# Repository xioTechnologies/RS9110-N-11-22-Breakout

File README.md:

RS9110-N-11-22-Breakout
=======================

Breakboard for the Redpine Signals [RS9110-N-11-22](http://www.redpinesignals.com/Modules/Internet_of_Things/Connection_Family/RS-9110-N-11-22.php) Wi-Fi module.  Includes pull-down resistors as per [datasheet](http://www.redpinesignals.com/pdfs/datasheets/RS9110-N-11-22_DataSheet.pdf) (pages 13-16).

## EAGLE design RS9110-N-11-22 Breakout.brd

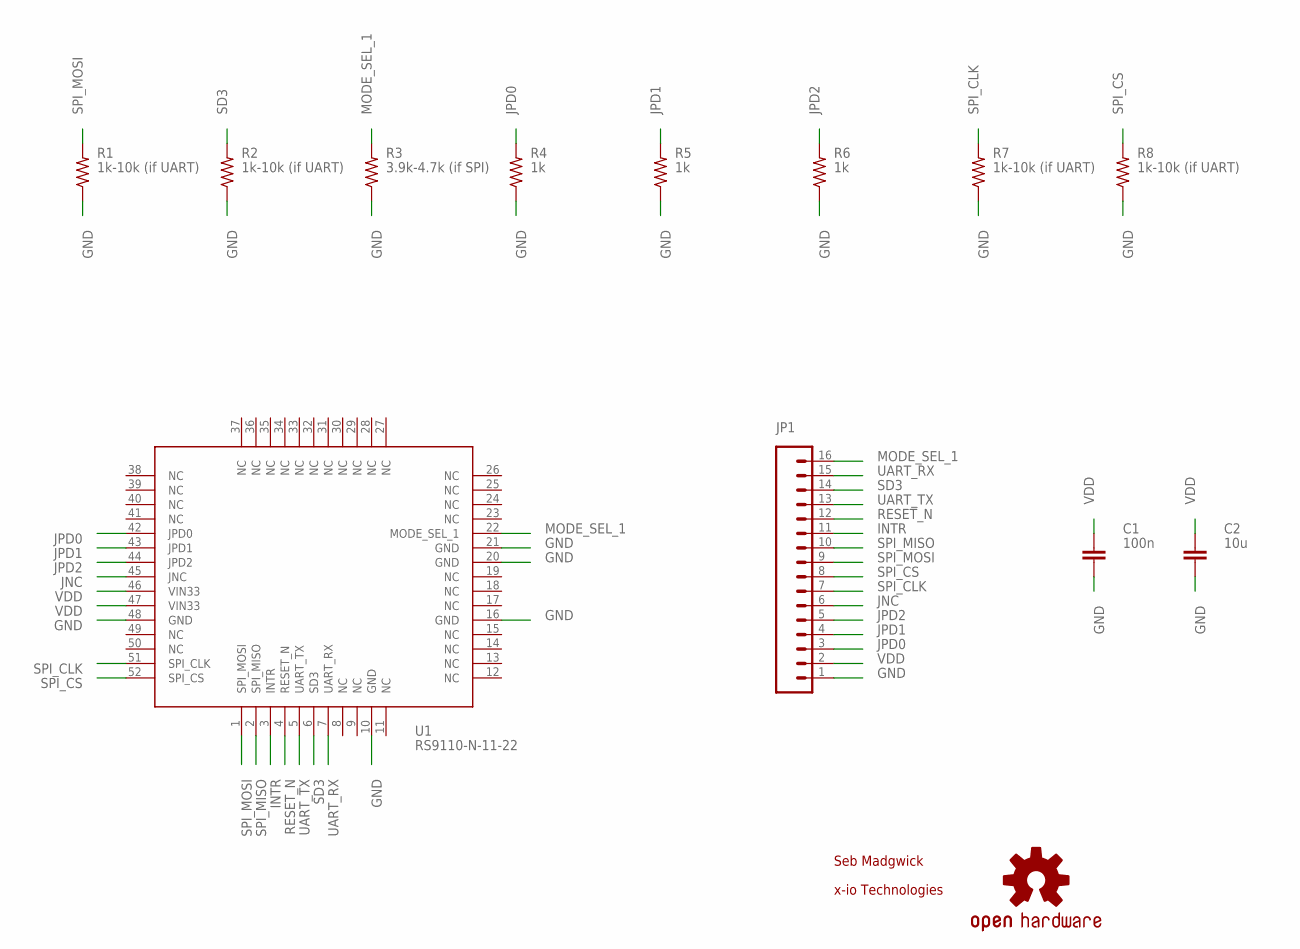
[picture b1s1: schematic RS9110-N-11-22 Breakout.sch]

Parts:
C1: 100n; 0603-CAP
C2: 10u; 0603-CAP
JP1: M16PTH; 1X16
LOGO1: OSHW-LOGOS; OSHW-LOGO-S
R1, R2, R7, R8: 1k-10k (if UART); 0603-RES
R3: 3.9k-4.7k (if SPI); 0603-RES
R4, R5, R6: 1k; 0603-RES
U1: RS9110-N-11-22

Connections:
GND: C1.2, C2.2, JP1.1, R1.1, R2.1, R3.1, R4.1, R5.1, R6.1, R7.1, R8.1, U1.10 (GND), U1.16 (GND), U1.20 (GND), U1.21 (GND), U1.48 (GND)
INTR: JP1.11, U1.3 (INTR)
JNC: JP1.6, U1.45 (JNC)
JPD0: JP1.3, R4.2, U1.42 (JPD0)
JPD1: JP1.4, R5.2, U1.43 (JPD1)
JPD2: JP1.5, R6.2, U1.44 (JPD2)
MODE_SEL_1: JP1.16, R3.2, U1.22 (MODE_SEL_1)
RESET_N: JP1.12, U1.4 (RESET_N)
SD3: JP1.14, R2.2, U1.6 (SD3)
SPI_CLK: JP1.7, R7.2, U1.51 (SPI_CLK)
SPI_CS: JP1.8, R8.2, U1.52 (SPI_CS)
SPI_MISO: JP1.10, U1.2 (SPI_MISO)
SPI_MOSI: JP1.9, R1.2, U1.1 (SPI_MOSI)
UART_RX: JP1.15, U1.7 (UART_RX)
UART_TX: JP1.13, U1.5 (UART_TX)
VDD: C1.1, C2.1, JP1.2, U1.46 (VIN33), U1.47 (VIN33)

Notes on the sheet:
Seb Madgwick
x-io Technologies

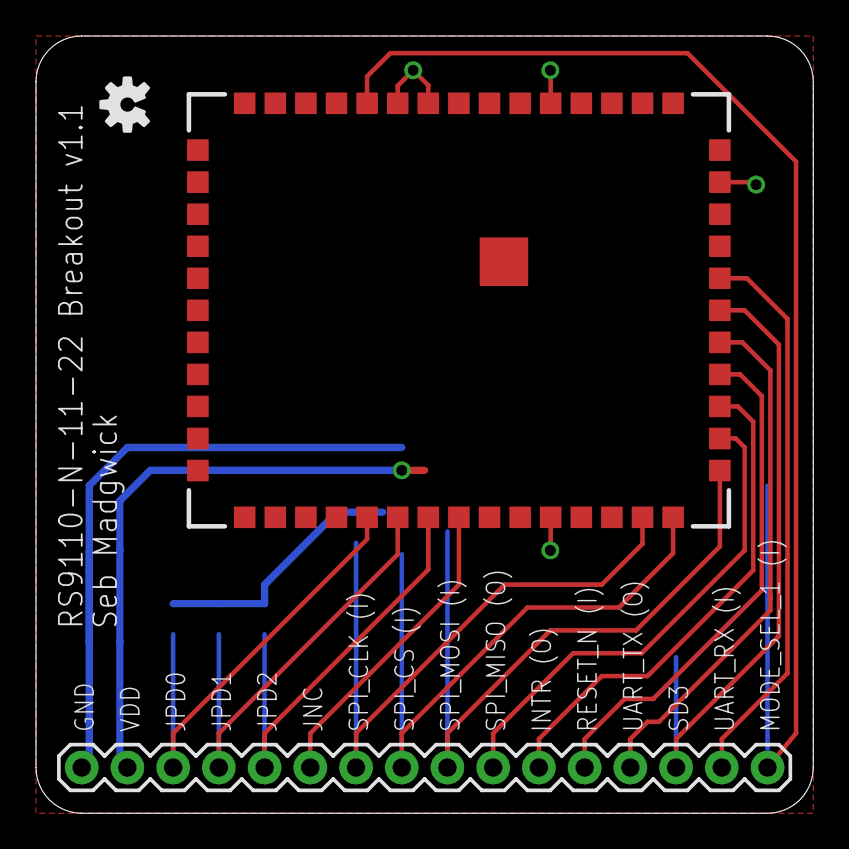
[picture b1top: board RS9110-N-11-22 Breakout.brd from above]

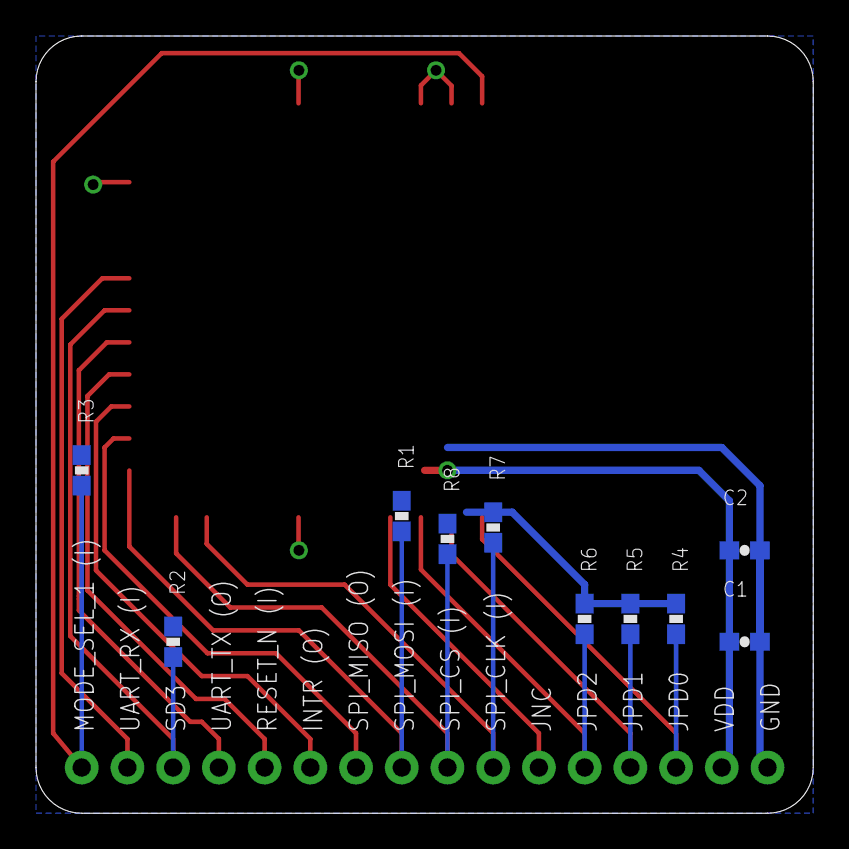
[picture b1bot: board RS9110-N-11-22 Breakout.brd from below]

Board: 2 copper layers, 43.2 x 43.2 mm, 13 parts (10 on the bottom side), 16 nets.

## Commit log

2014-10-24 Add project files
2014-10-24 Correct files names
2014-10-24 Add notes about when to populate resistors
2014-10-26 Remove copper from around antenna
2014-11-17 Add PCB photo

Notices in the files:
parts and their libraries:
SparkFun-Aesthetics: Licensing: Creative Commons ShareAlike 4.0 International - https://creativecommons.org/licenses/by-sa/4.0
